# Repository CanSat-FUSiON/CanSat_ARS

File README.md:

# CanSat_ARS-1.00

**Present Version : ARS-1.00**
誰かが個人単位でリファクタリングやデバッグしたら+0.01，ミッションぐるみで大型アップデートをしたら+1.00して小数部切り捨て．
編集したら更新すること
ToDoはここに記すと管理しやすい：https://github.com/orgs/CanSat-FUSiON/projects/5/views/1?layout=board

## ディレクトリ説明
|ディレクトリ名|説明|
|----|----|
|Design-Data|CanSatの設計データが格納されています．CanSatを自分の好きなようにアレンジする場合にはこちらのディレクトリを操作してください．|
|Operation-Guide|CanSatの保守運用に関するデータが格納されています．機器の組立てと運用を行う場合はこのディレクトリのみ覗けば大丈夫です．|

## 命名規則
ディレクトリ名は原則，頭文字のみ大文字(複数単語は"-"で接続)
ファイル名は小文字統一

マークダウンファイルはGitHub直下のみ`README.md`とし(本ファイル)，それ以下の階層ではファイルの内容に従って命名する．
例）`./Design-Data/Hardware/`におけるハードウェア機器の構成を説明するためのマークダウンファイルは`ハードウェア機器の構成.md`

## コーディング規則
開発に使う言語としてpythonを用いる．
ただし，OBCの変更や機能拡張に伴い要求が変わる場合その限りではない．
pythonにおけるコーディング規約として，[pep8](https://pep8-ja.readthedocs.io/ja/latest/)にしたがう．

## ブランチの使い方
大会の出場の途中などで頻繁な更新が想定される際は，`main`の代理となる別な開発ブランチを設けること．
その場合，審査書提出後や，大会期間が終了時など，変更が安定した時点で開発ブランチを`main`にマージすること．
例）Mission4の開発期間中→`dev-m4`などと名付け暫定的な`main`の代わりとして用いる．

## コミットメッセージ
コミットメッセージは以下の4種類から適切なものを選び **(作業対象)+(: )+(作業分類)+(半角スペース)+(作業内容)** と書く．
例）`zero: Add telecomunication driver`
|作業分類|説明|
|----|-----|
|fix|バグ修正|
|add|新規(ファイル)機能追加|
|update|機能修正(バグではない)|
|remove|削除(ファイル)|

※（参考）https://qiita.com/itosho/items/9565c6ad2ffc24c09364

## ライセンス
This repository is released under the MIT License, see LICENSE.txt.

このリポジトリはMITライセンスのもとで公開されている． 'LISENCE.txt'を参照．

## バージョン管理
|Ver.|内容|
|----|----|
|1.00|Mission2終了時点の完成形CanSat|
|||

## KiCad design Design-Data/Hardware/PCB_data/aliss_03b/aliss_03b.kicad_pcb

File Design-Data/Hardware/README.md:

# Hardware
FUSiONのCanSat Model ARS系統のハードウェア設計

## ピンアサイン

更新する際は[こちらのスプレッドシート](https://docs.google.com/spreadsheets/d/1eQN7OE-Z9ALaf2SgiwYws5UZOM_eGH8C7UVVMnbFOFw/edit#gid=0)をコピーしてスクリーンショットを添付して下さい  

## 部品リスト
用いた代表的な部品は以下の通り．
具体的な型番などは別ファイルで示す．
|部品名|用途|
|----|----|
|温湿度気圧センサ|気温・気圧から高度を測定|
|9軸センサ|自身の向きの確認．及び転倒やスタック検知|
|GPSセンサ|自身の座標の確認．|
|モーター|走行やスタックからの脱出．|

以下に詳細な部品リストを表示する

|名前|型番|用途|数|
|----|----|----|----|
|||||

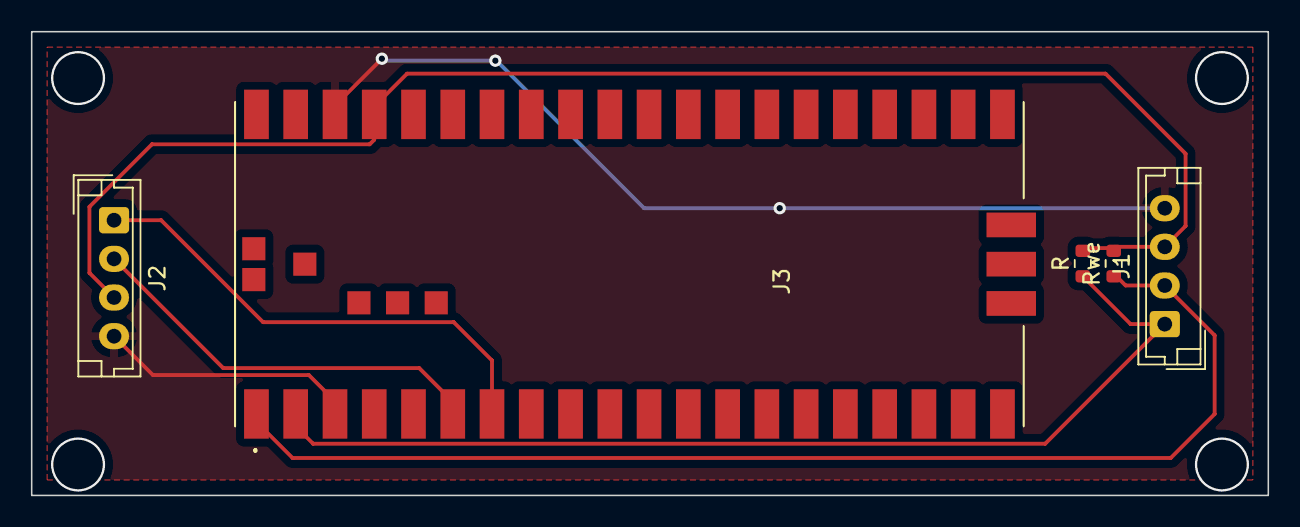
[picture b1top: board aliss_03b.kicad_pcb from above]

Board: 2 copper layers, 80.0 x 30.0 mm, 5 parts (0 on the bottom side), 6 nets.

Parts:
J1, J2: Conn_01x04_Shielded; JST_EH_B4B-EH-A_1x04_P2.50mm_Vertical
J3: Conn_02x20_Counter_Clockwise; RaspberryPiPico
R: 10k; R_0603_1608Metric
Rwe: 10k; R_0603_1608Metric

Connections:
/3V3: J1.3, J2.3, J3.37, R.2, Rwe.2
/GND: J1.4, J2.4, J3.3, J3.38
/Rx: J2.2, J3.6
/SCL: J1.1, J3.2, R.1
/SDA: J1.2, J3.1, Rwe.1
/Tx: J2.1, J3.7

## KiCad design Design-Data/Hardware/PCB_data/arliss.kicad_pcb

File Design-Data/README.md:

# Design-Data

ARSモデルの設計データを記載する．
現在のディレクトリは以下のように分けられる．
|ファイル名|説明|
|----|----|
|Mechanic|機体構造や試験によって判明した物理特性に関するデータを記載する．|
|Hardware|組み込みハードウェア分野についての設計データを集める．マイコンとセンサ，アクチュエータなどの電気的な接続やPCBデータなど．|
|Software|組み込みソフトウェアや画像処理分野の設計データを集める．|

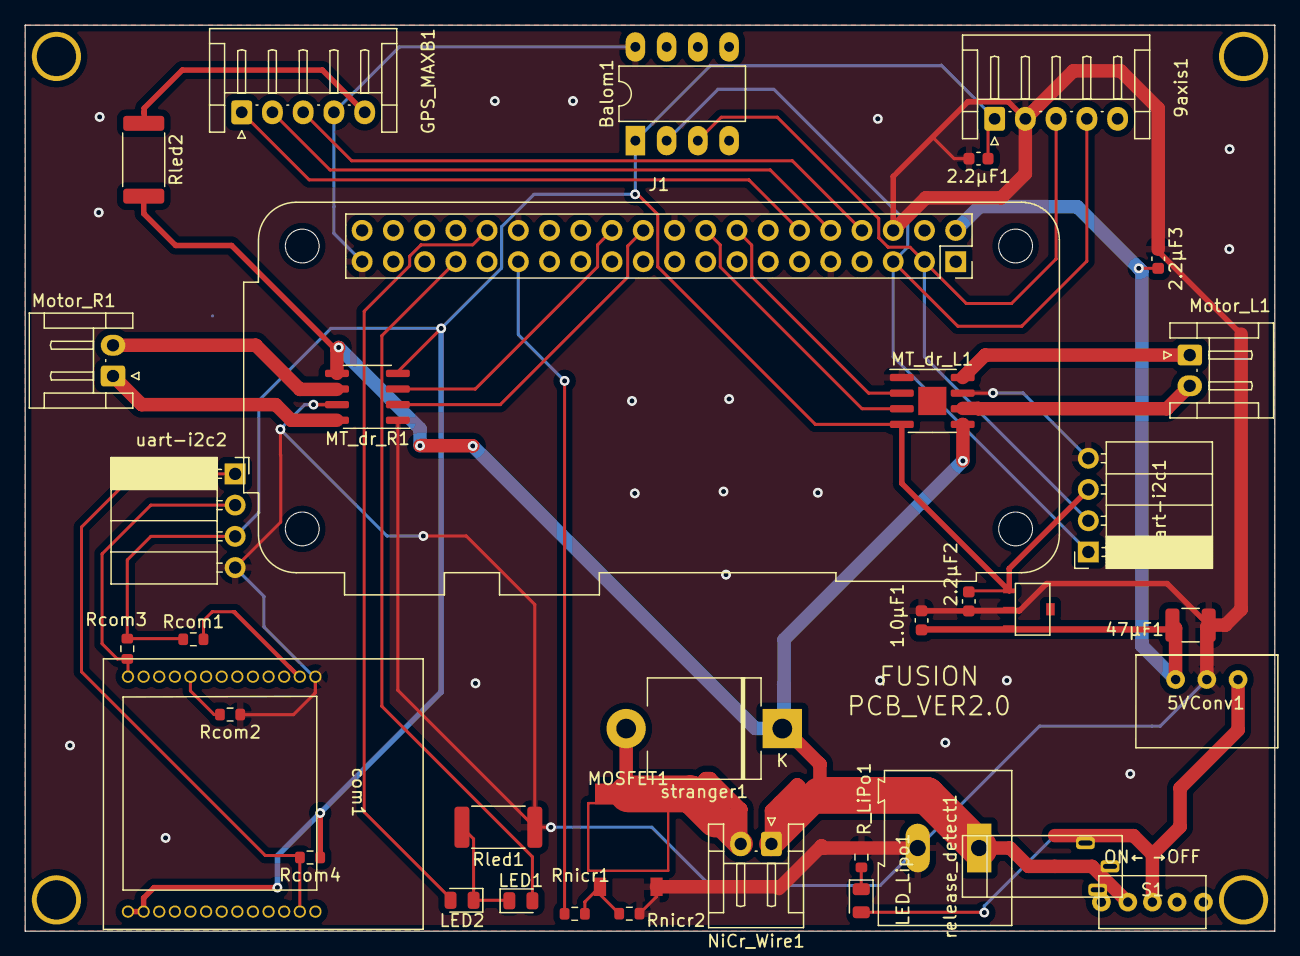
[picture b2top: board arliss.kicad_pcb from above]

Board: 2 copper layers, 101.6 x 73.7 mm, 36 parts (0 on the bottom side), 30 nets.

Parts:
1.0μF1, 2.2μF1, 2.2μF2, 2.2μF3: C; C_0603_1608Metric
5VConv1: M78AR05-1
9axis1: Conn_01x05; JST_EH_S5B-EH_1x05_P2.50mm_Horizontal
47μF1: C; C_1210_3225Metric
Balom1: Conn_02x04; DIP-8_W7.62mm_LongPads
GPS_MAXB1: Conn_01x05; JST_EH_S5B-EH_1x05_P2.50mm_Horizontal
J1: Raspberry_Pi_zero; Raspberry_Pi_Zero_Socketed_THT_FaceDown_MountingHoles
J2: Conn_01x02; TerminalBlock_Altech_AK300-2_P5.00mm
LED1, LED2: OSR50805C1C; LED_0805_2012Metric
LED_Lipo1: OSR50805C1C; LED_0805_2012Metric
MOSFET1: TK25S06N1L; TK25s06N1L
MT_dr_L1: TB67H450FNG,EL; HSOP-8-1EP_3.9x4.9mm_P1.27mm_EP2.3x2.3mm
MT_dr_R1: TB67H450FNG,EL; HSOP-8-1EP_3.9x4.9mm_P1.27mm_EP2.3x2.3mm
Motor_L1: Conn_01x02; JST_EH_S2B-EH_1x02_P2.50mm_Horizontal
Motor_R1: Conn_01x02; JST_EH_S2B-EH_1x02_P2.50mm_Horizontal
NiCr_Wire1: Conn_01x02; JST_EH_S2B-EH_1x02_P2.50mm_Horizontal
R_LiPo1: 10k; R_0603_1608Metric
Rcom1, Rcom2, Rcom3, Rcom4: 10k; R_0603_1608Metric
Rled1, Rled2: 200; R_2512_6332Metric
Rnicr1: 1k; R_0603_1608Metric
Rnicr2: 10k; R_0603_1608Metric
S1: SK-12D11VG3
U2: 3V3Reg/NJW4183U3; NJW4183U3-33B
com1: RM92A; RM-92A
release_detect1: Conn_01x02; Release_Sensor
stranger1: DIODE; D_5KPW_P12.70mm_Horizontal
uart-i2c1, uart-i2c2: Conn_01x04; PinSocket_1x04_P2.54mm_Horizontal

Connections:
/SCL: 9axis1.4, Balom1.2, J1.5 (SCL/GPIO3), uart-i2c1.1
/SDA: 9axis1.3, Balom1.3, J1.3 (SDA/GPIO2), uart-i2c1.2
/ToMotor: J2.1, MT_dr_L1.5 (VM), MT_dr_R1.5 (VM), NiCr_Wire1.2, Rled2.2, release_detect1.1, stranger1.2 (A)
/UART_Rx: Rcom4.2, com1.25, uart-i2c2.1
/UART_Tx: Rcom3.2, com1.13, uart-i2c2.2
unnamed: 5VConv1.1 (+VIN), LED_Lipo1.2, release_detect1.2
unnamed: GPS_MAXB1.1, J1.12 (GPIO18/PWM0)
unnamed: GPS_MAXB1.2, J1.10 (GPIO15/RXD)
unnamed: GPS_MAXB1.3, J1.8 (GPIO14/TXD)
unnamed: GPS_MAXB1.5, Rled2.1
unnamed: J1.16 (GPIO23), MT_dr_R1.3 (IN1)
unnamed: J1.18 (GPIO24), MT_dr_R1.2 (IN2)
unnamed: J1.22 (GPIO25), MT_dr_L1.2 (IN2)
unnamed: J1.24 (~CE0/GPIO8), MT_dr_L1.3 (IN1)
unnamed: J1.29 (GCLK1/GPIO5), Rnicr1.2
unnamed: J1.32 (PWM0/GPIO12), LED2.2
unnamed: J1.33 (PWM1/GPIO13), LED1.2
unnamed: LED1.1, LED2.1, Rled1.2
unnamed: LED_Lipo1.1, R_LiPo1.2
unnamed: MOSFET1.1, Rnicr1.1, Rnicr2.2
unnamed: MOSFET1.2, NiCr_Wire1.1, stranger1.1 (K)
unnamed: MT_dr_L1.6 (OUT1), Motor_L1.2
unnamed: MT_dr_L1.8 (OUT2), Motor_L1.1
unnamed: MT_dr_R1.6 (OUT1), Motor_R1.2
unnamed: MT_dr_R1.8 (OUT2), Motor_R1.1
unnamed: Rcom1.2, com1.2
unnamed: Rcom2.2, com1.9
RasPi_Vcc: 1.0μF1.2, 2.2μF3.2, 5VConv1.3 (+VOUT), 47μF1.2, J1.2 (5V), U2.3 (Vin)
Raspi_GND: 1.0μF1.1, 2.2μF1.2, 2.2μF2.1, 2.2μF3.1, 5VConv1.2 (GND), 9axis1.2, 47μF1.1, Balom1.8, GPS_MAXB1.4, J1.6 (GND), J1.9 (GND), J1.20 (GND), J1.30 (GND), J1.39 (GND), J2.2, MOSFET1.3, MT_dr_L1.1 (GND), MT_dr_L1.7 (RS), MT_dr_R1.1 (GND), MT_dr_R1.7 (RS), R_LiPo1.1, Rcom2.1, Rled1.1, Rnicr2.1, U2.2 (GND), com1.1, uart-i2c1.4, uart-i2c2.4
Sensor_Vcc: 2.2μF1.1, 2.2μF2.2, 9axis1.1, Balom1.1, MT_dr_L1.4 (VREF), MT_dr_R1.4 (VREF), Rcom1.1, Rcom3.1, Rcom4.1, U2.1 (Vout), com1.14, com1.15, uart-i2c1.3, uart-i2c2.3

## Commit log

2023-06-13 組み込み統合プロブラムとその説明文を追加した。
2023-06-13 組み込みプログラムとその説明文を追加した。
2023-06-13 モータの動作プログラムを作成した
2023-06-13 モータードライバー用のテストプログラムの作製
2023-06-13 Delete Design-Data/Software/Component-Test/MotorDriver directory
    ごめんなさい．プッシュする先間違えたので削除します
2023-06-19 9軸と気圧を追加
2023-06-19 READMEの追加
2023-06-19 回路図データアップロード
2023-06-25 メインのコメントアウトを加えました。
2023-06-25 Cadデータをパーツに分けて追加した。
2023-07-31 GPSの追加
2023-08-01 コメントアウトを加えました。 部品の購入リンクやデータシートをまとめました。
2023-08-01 CanSatの組み上げ書類を作成しました．
2023-08-06 add the link of GPS.
2023-08-07 rm92a追加
2023-08-07 parachute hoetomaking
2023-08-14 how to making parachute
2023-08-14 軽微修正
2023-08-15 ファイル整理done
2023-08-21 組み上げ書の更新(pdf化，md，画像の削除)
2023-08-21 motor.pyを修正しました
2023-08-28 パラコード,畳み方についての記述追加
2023-08-30 RM92Aまわりについて記入
2023-08-30 Add files via upload
    add setting
2023-08-30 最終修正(確認必要)
2023-08-30 最終修正(確認必要2)
2023-08-30 最終修正(画像サイズ調整)
2023-09-06 無線について追加
    無線について追加
2023-09-06 エンベロープ作成方法記載
2023-09-06 CanSat組み上げ書に配線部分を追加した
2023-09-06 README: Add rules
2023-09-06 Operation-Control; Fix indention added
    改行されていない部分の改行を行なった
2023-09-06 Operation-Control; Fix indention added
2023-09-06 Operations-Control; Fix indention fixed
2023-09-11 エンベロープ作成方法記載2
2023-09-11 エンベロープ作成方法記載3
2023-09-12 MD 画像追加の確認
2023-09-12 画像の確認
2023-09-12 画像の追加
2023-09-12 dev-m2-ob: update エンベロープの作成方法について加筆しました
2023-09-12 RM92A: Fix images added
2023-09-12 Design-Data: add CanSat_buildup_ver3.pdf
2023-09-12 RM92A: Fix images and comment added
2023-09-12 Operation Control: Fix Link Added
2023-09-13 dev-m2-ob: fix 挿絵・文言など修正
2023-09-25 all: sort out
2023-09-27 all: fix filename
2023-09-27 Envelope: Fix expression
    エンベロープの文章の中で誤った情報や
    誤字があったので修正しました。
2023-10-27 add MIT Lisence
